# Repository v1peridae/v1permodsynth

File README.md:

# This is the v1permodsyth

- A modular sythesiser is an electronic music instrument made of different sythesiser modules! (who wouldve guessed)
- They look something like this:

<p align="center">
  <br>
  <sub>(mine doesn't look as fancy but we're getting somewhere lol)</sub>
</p>

### it currently has:
- square vco

- vca

- guitar input

-ar

-4lfo

-fm drums

## more on the process
i've never really made anything this complex so i totally understand if it might not work on the first go but i'm really happy with how far i've gotten with this. if you'd like to learn more about the making process check out my JOURNAL.md 

credits to https://www.bartonmusicalcircuits.com/ which is where i learnt how to do all of this :)

casing - it currently doesnt have a case but i have all the measurements and hope to build a wooden or hard cardboard case

note on commits:
guh it totally skipped my mind to make frequent commits of this so i accept my fate if it means my hours get reduced since this is one is on me.

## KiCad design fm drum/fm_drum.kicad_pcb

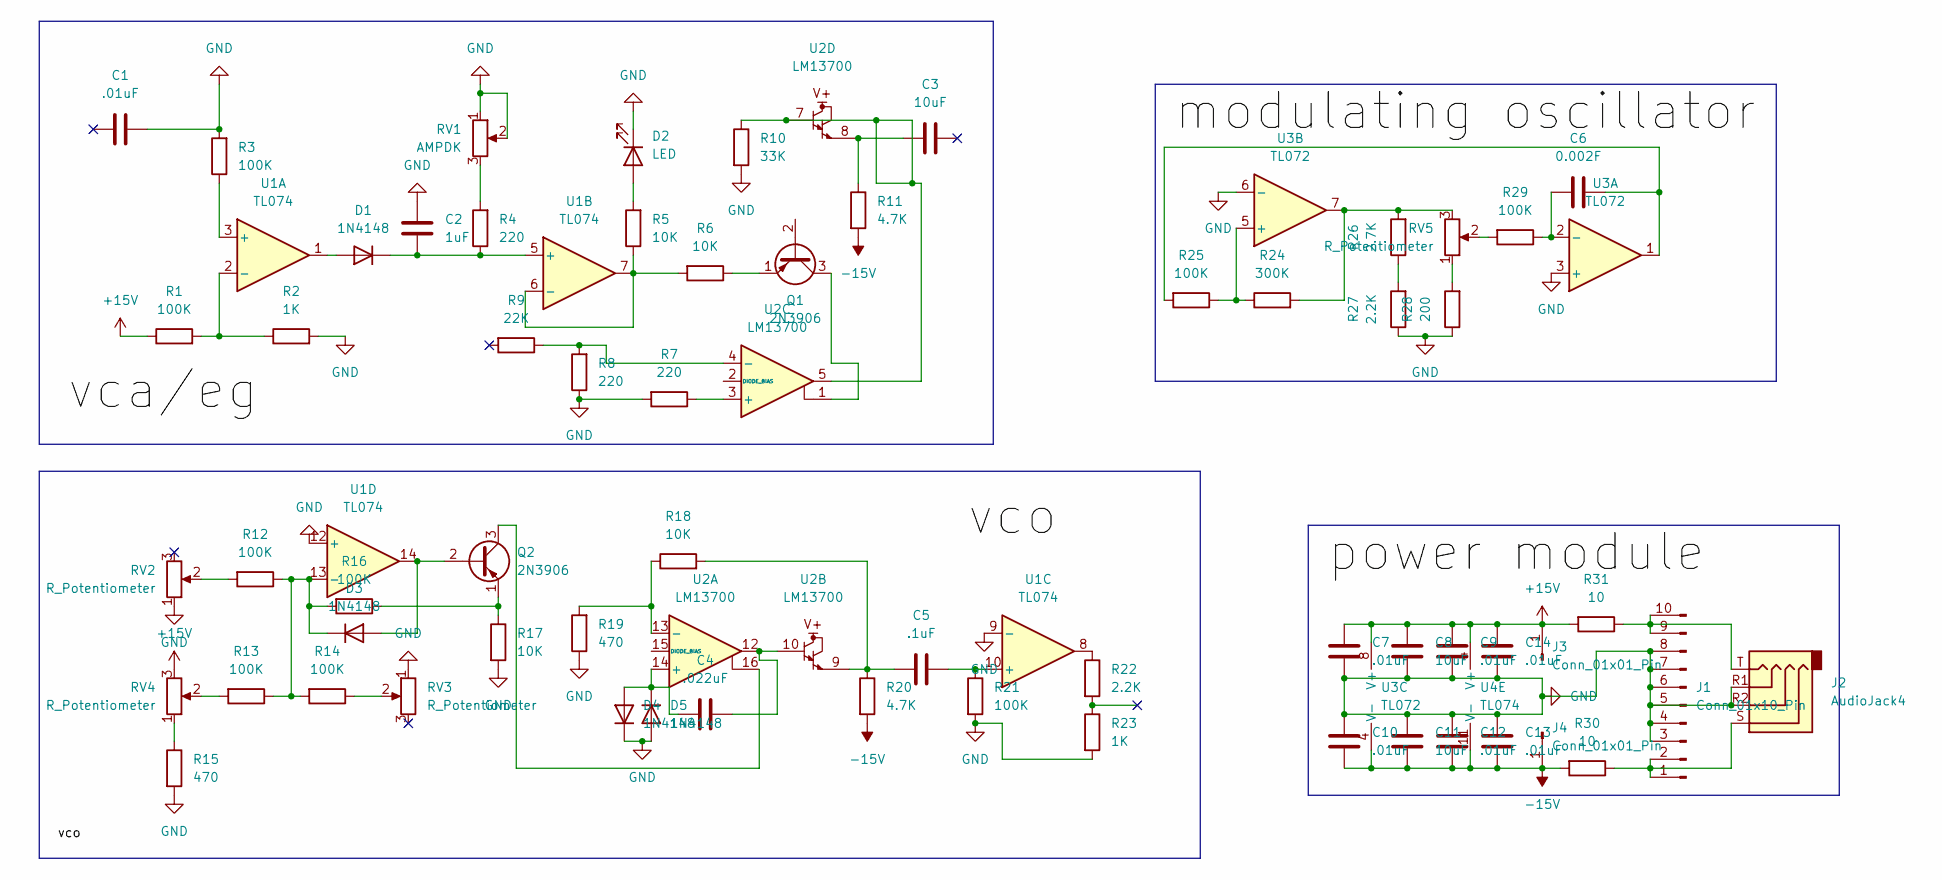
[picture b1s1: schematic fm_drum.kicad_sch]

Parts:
C1, C7, C9, C10, C12, C13, C14: .01uF; C_Disc_D3.8mm_W2.6mm_P2.50mm
C2: 1uF; CP_Radial_D5.0mm_P2.00mm
C3, C8, C11: 10uF; CP_Radial_D5.0mm_P2.50mm
C4: .022uF; C_Rect_L7.2mm_W2.5mm_P5.00mm_FKS2_FKP2_MKS2_MKP2
C5: .1uF; C_Rect_L7.2mm_W2.5mm_P5.00mm_FKS2_FKP2_MKS2_MKP2
C6: 0.002F; C_Rect_L7.2mm_W2.5mm_P5.00mm_FKS2_FKP2_MKS2_MKP2
D1, D3, D4, D5: 1N4148; D_DO-35_SOD27_P7.62mm_Horizontal
D2: LED; LED_D3.0mm
J1: Conn_01x10_Pin; IDC-Header_2x05_P2.54mm_Vertical
J2: AudioJack4; Jack_3.5mm_QingPu_WQP-PJ398SM_Vertical_CircularHoles
J3, J4: Conn_01x01_Pin; PinHeader_1x01_P2.54mm_Horizontal
Q1, Q2: 2N3906; TO-92_Inline
R1, R3, R12, R13, R14, R16, R21, R25, R29: 100K; R_Axial_DIN0207_L6.3mm_D2.5mm_P7.62mm_Horizontal
R2, R23: 1K; R_Axial_DIN0207_L6.3mm_D2.5mm_P7.62mm_Horizontal
R4, R7, R8: 220; R_Axial_DIN0207_L6.3mm_D2.5mm_P7.62mm_Horizontal
R5, R6, R17, R18: 10K; R_Axial_DIN0207_L6.3mm_D2.5mm_P7.62mm_Horizontal
R9: 22K; R_Axial_DIN0207_L6.3mm_D2.5mm_P7.62mm_Horizontal
R10: 33K; R_Axial_DIN0207_L6.3mm_D2.5mm_P7.62mm_Horizontal
R11, R20: 4.7K; R_Axial_DIN0207_L6.3mm_D2.5mm_P7.62mm_Horizontal
R15, R19: 470; R_Axial_DIN0207_L6.3mm_D2.5mm_P7.62mm_Horizontal
R22, R27: 2.2K; R_Axial_DIN0207_L6.3mm_D2.5mm_P7.62mm_Horizontal
R24: 300K; R_Axial_DIN0207_L6.3mm_D2.5mm_P7.62mm_Horizontal
R26: 2.7K; R_Axial_DIN0207_L6.3mm_D2.5mm_P7.62mm_Horizontal
R28: 200; R_Axial_DIN0207_L6.3mm_D2.5mm_P7.62mm_Horizontal
R30, R31: 10; R_Axial_DIN0207_L6.3mm_D2.5mm_P7.62mm_Horizontal
RV1: AMPDK; Potentiometer_Alps_RK163_Single_Horizontal
RV2, RV3, RV4, RV5: R_Potentiometer; Potentiometer_Alps_RK163_Single_Horizontal
U1, U4: TL074; DIP-14_W7.62mm
U2: LM13700; SOIC-16_3.9x9.9mm_P1.27mm
U3: TL072; DIP-8-16_W7.62mm

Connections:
+15V: C7.2, C8.2, C9.2, C14.2, J3.1, R1.1, R31.2, RV4.3, U3.8 (V+), U4.4 (V+)
-15V: C10.1, C11.1, C12.1, C13.1, J4.1, R11.2, R20.2, R30.2, U3.4 (V-), U4.11 (V-)
GND: C1.2, C2.2, C7.1, C8.1, C9.1, C10.2, C11.2, C12.2, C13.2, C14.1, D2.1 (K), D4.1 (K), D5.2 (A), J1.3, J1.4, J1.5, J1.6, J1.7, J1.8, J2.R1, J2.R2, R2.2, R3.2, R7.2, R8.1, R10.2, R15.2, R17.2, R19.1, R21.2, R23.2, R27.1, R28.1, RV1.1, RV1.2, RV2.1, RV3.1, U1.9 (-), U1.12 (+), U3.3 (+), U3.6 (-)
unnamed: C3.2, R11.1, U2.8
unnamed: C4.2, U2.10, U2.12
unnamed: C5.1, R18.2, R20.1, U2.9
unnamed: C6.2, R25.2, U3.1
unnamed: D1.2 (A), U1.1
unnamed: C2.1, D1.1 (K), R4.1, U1.5 (+)
unnamed: D2.2 (A), R5.2
unnamed: D3.2 (A), Q2.2 (B), U1.14
unnamed: D3.1 (K), R12.1, R13.1, R14.2, R16.2, U1.13 (-)
unnamed: C4.1, D4.2 (A), D5.1 (K), U2.14 (+)
unnamed: J1.1, J1.2, J2.S, R30.1
unnamed: J1.9, J1.10, J2.T, R31.1
unnamed: Q1.3 (C), U2.1
unnamed: Q1.1 (E), R6.1
unnamed: Q2.3 (C), U2.16
unnamed: Q2.1 (E), R16.1, R17.1
unnamed: R4.2, RV1.3
unnamed: R10.1, U2.5, U2.7
unnamed: R12.2, RV2.2
unnamed: R13.2, RV4.2
unnamed: R14.1, RV3.2
unnamed: R15.1, RV4.1
unnamed: R22.1, U1.8
unnamed: R24.2, R26.2, RV5.3, U3.7
unnamed: R26.1, R27.2
unnamed: R28.2, RV5.1
unnamed: R29.2, RV5.2
unnamed: R3.1, U1.3 (+)
unnamed: R1.2, R2.1, U1.2 (-)
unnamed: R5.1, R6.2, U1.6 (-), U1.7
unnamed: C5.2, R21.1, U1.10 (+)
unnamed: R18.1, R19.2, U2.13 (-)
unnamed: R7.1, U2.3 (+)
unnamed: R8.2, R9.1, U2.4 (-)
unnamed: C6.1, R29.1, U3.2 (-)
unnamed: R24.1, R25.1, U3.5 (+)

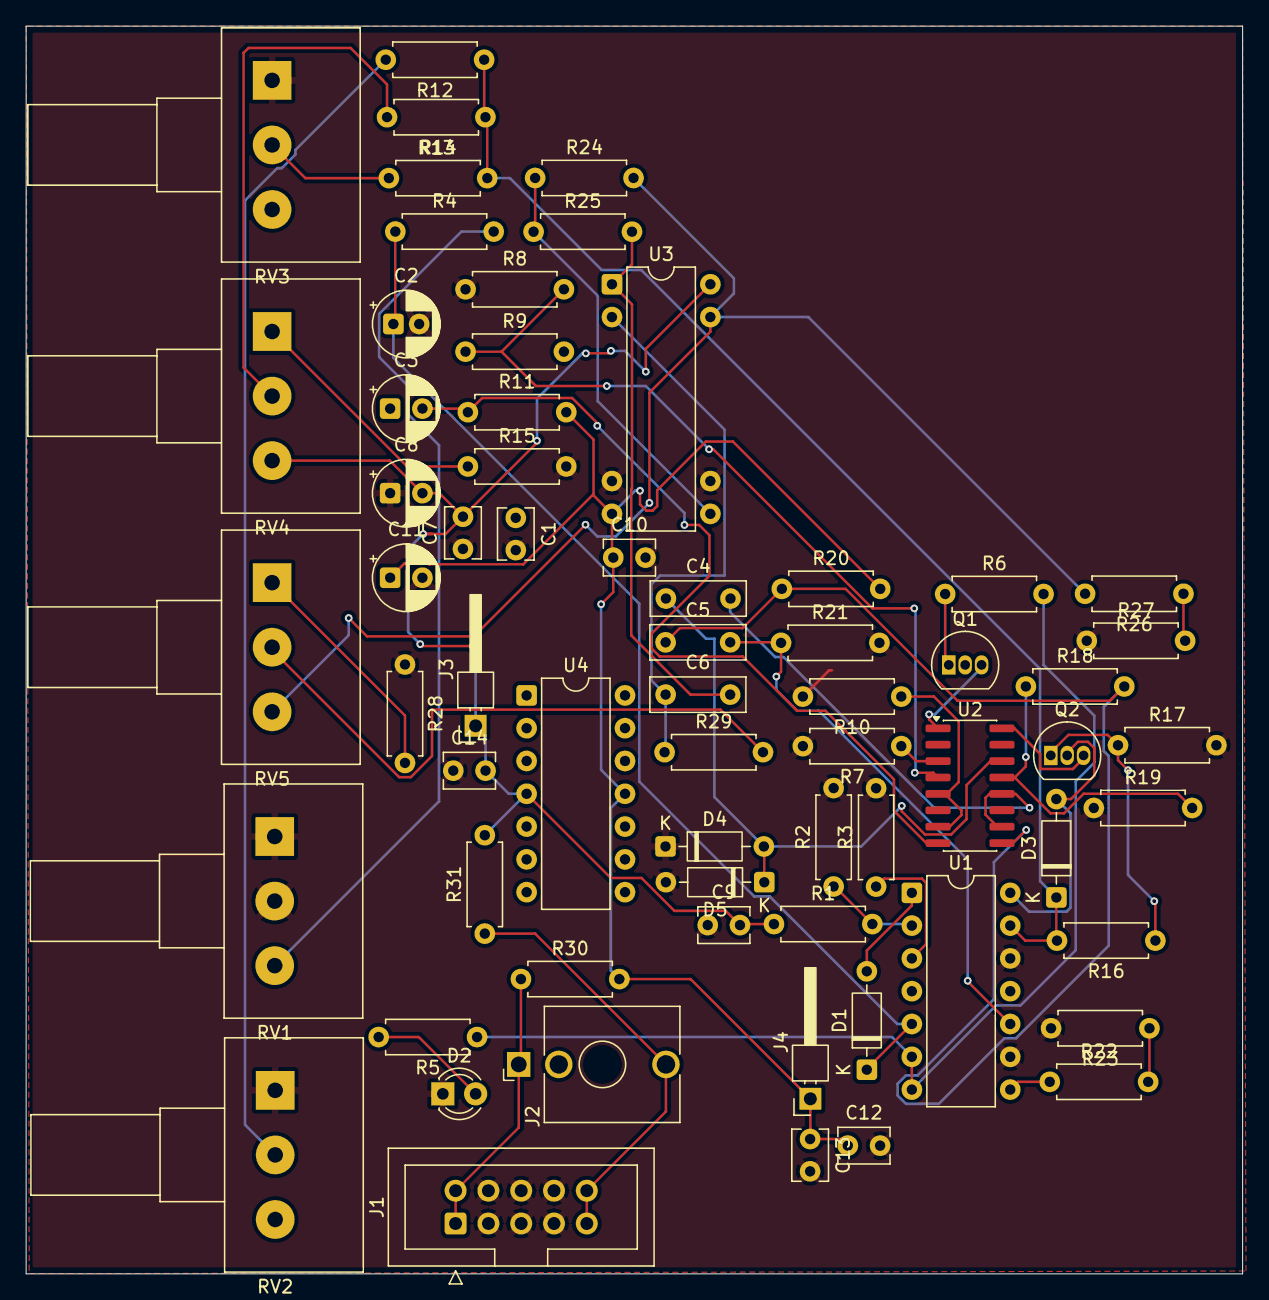
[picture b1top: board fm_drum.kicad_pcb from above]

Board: 2 copper layers, 94.2 x 96.6 mm, 65 parts (0 on the bottom side), 39 nets.

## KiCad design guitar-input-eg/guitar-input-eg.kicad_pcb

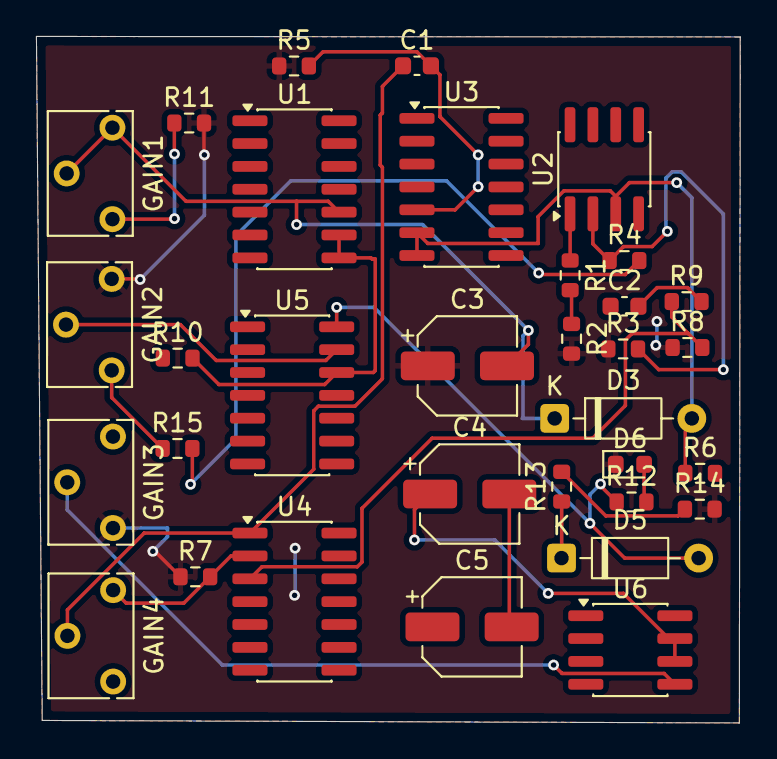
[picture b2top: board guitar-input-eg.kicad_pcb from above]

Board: 2 copper layers, 39.1 x 38.1 mm, 34 parts (1 on the bottom side), 21 nets.

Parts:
.: LOGO
C1, C2: 1uF; C_0603_1608Metric
C3, C4, C5: 10uF; CP_Elec_5x5.4
D3, D5: 1N4148; D_DO-35_SOD27_P7.62mm_Horizontal
D6: LED; LED_0603_1608Metric
GAIN1, GAIN2, GAIN3, GAIN4: A1M; Potentiometer_Bourns_3266W_Vertical
R1, R13: 1.5K; R_0603_1608Metric
R2, R3, R6, R7, R10, R12, R14: 1K; R_0603_1608Metric
R4, R5, R8, R11, R15: 100K; R_0603_1608Metric
R9: 470K; R_0603_1608Metric
U1, U3, U4, U5: TL074; SOIC-14_3.9x8.7mm_P1.27mm
U2, U6: TL072; SOIC-8_3.9x4.9mm_P1.27mm

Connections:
+15V: R4.2, R15.2
GND: C3.1, D6.1 (K), GAIN2.3, GAIN3.1, R2.2, R3.1, R5.1, R7.1, R8.1, R11.2, R14.2
unnamed: C1.1, GAIN4.2, U4.1
unnamed: C2.2, R9.2
unnamed: C4.2, C5.2
unnamed: D3.2 (A), R6.1, U2.3 (+), U3.6 (-), U3.7
unnamed: C3.2, D3.1 (K), GAIN1.2, GAIN1.3, U1.10 (+)
unnamed: D5.2 (A), R12.1, U5.14
unnamed: D5.1 (K), R13.1
unnamed: D6.2 (A), R12.2
unnamed: GAIN1.1, R11.1
unnamed: GAIN2.1, R15.1
unnamed: R1.1, U2.1
unnamed: R10.2, U1.8, U1.9 (-), U5.12 (+)
unnamed: R3.2, R4.1, U2.2 (-)
unnamed: C1.2, R5.2, U3.5 (+)
unnamed: R8.2, R9.1, U4.3 (+)
unnamed: GAIN4.3, R7.2, U4.2 (-)
unnamed: GAIN2.2, U5.13 (-)
unnamed: GAIN3.2, U6.5 (+)
unnamed: C4.1, U6.6 (-), U6.7

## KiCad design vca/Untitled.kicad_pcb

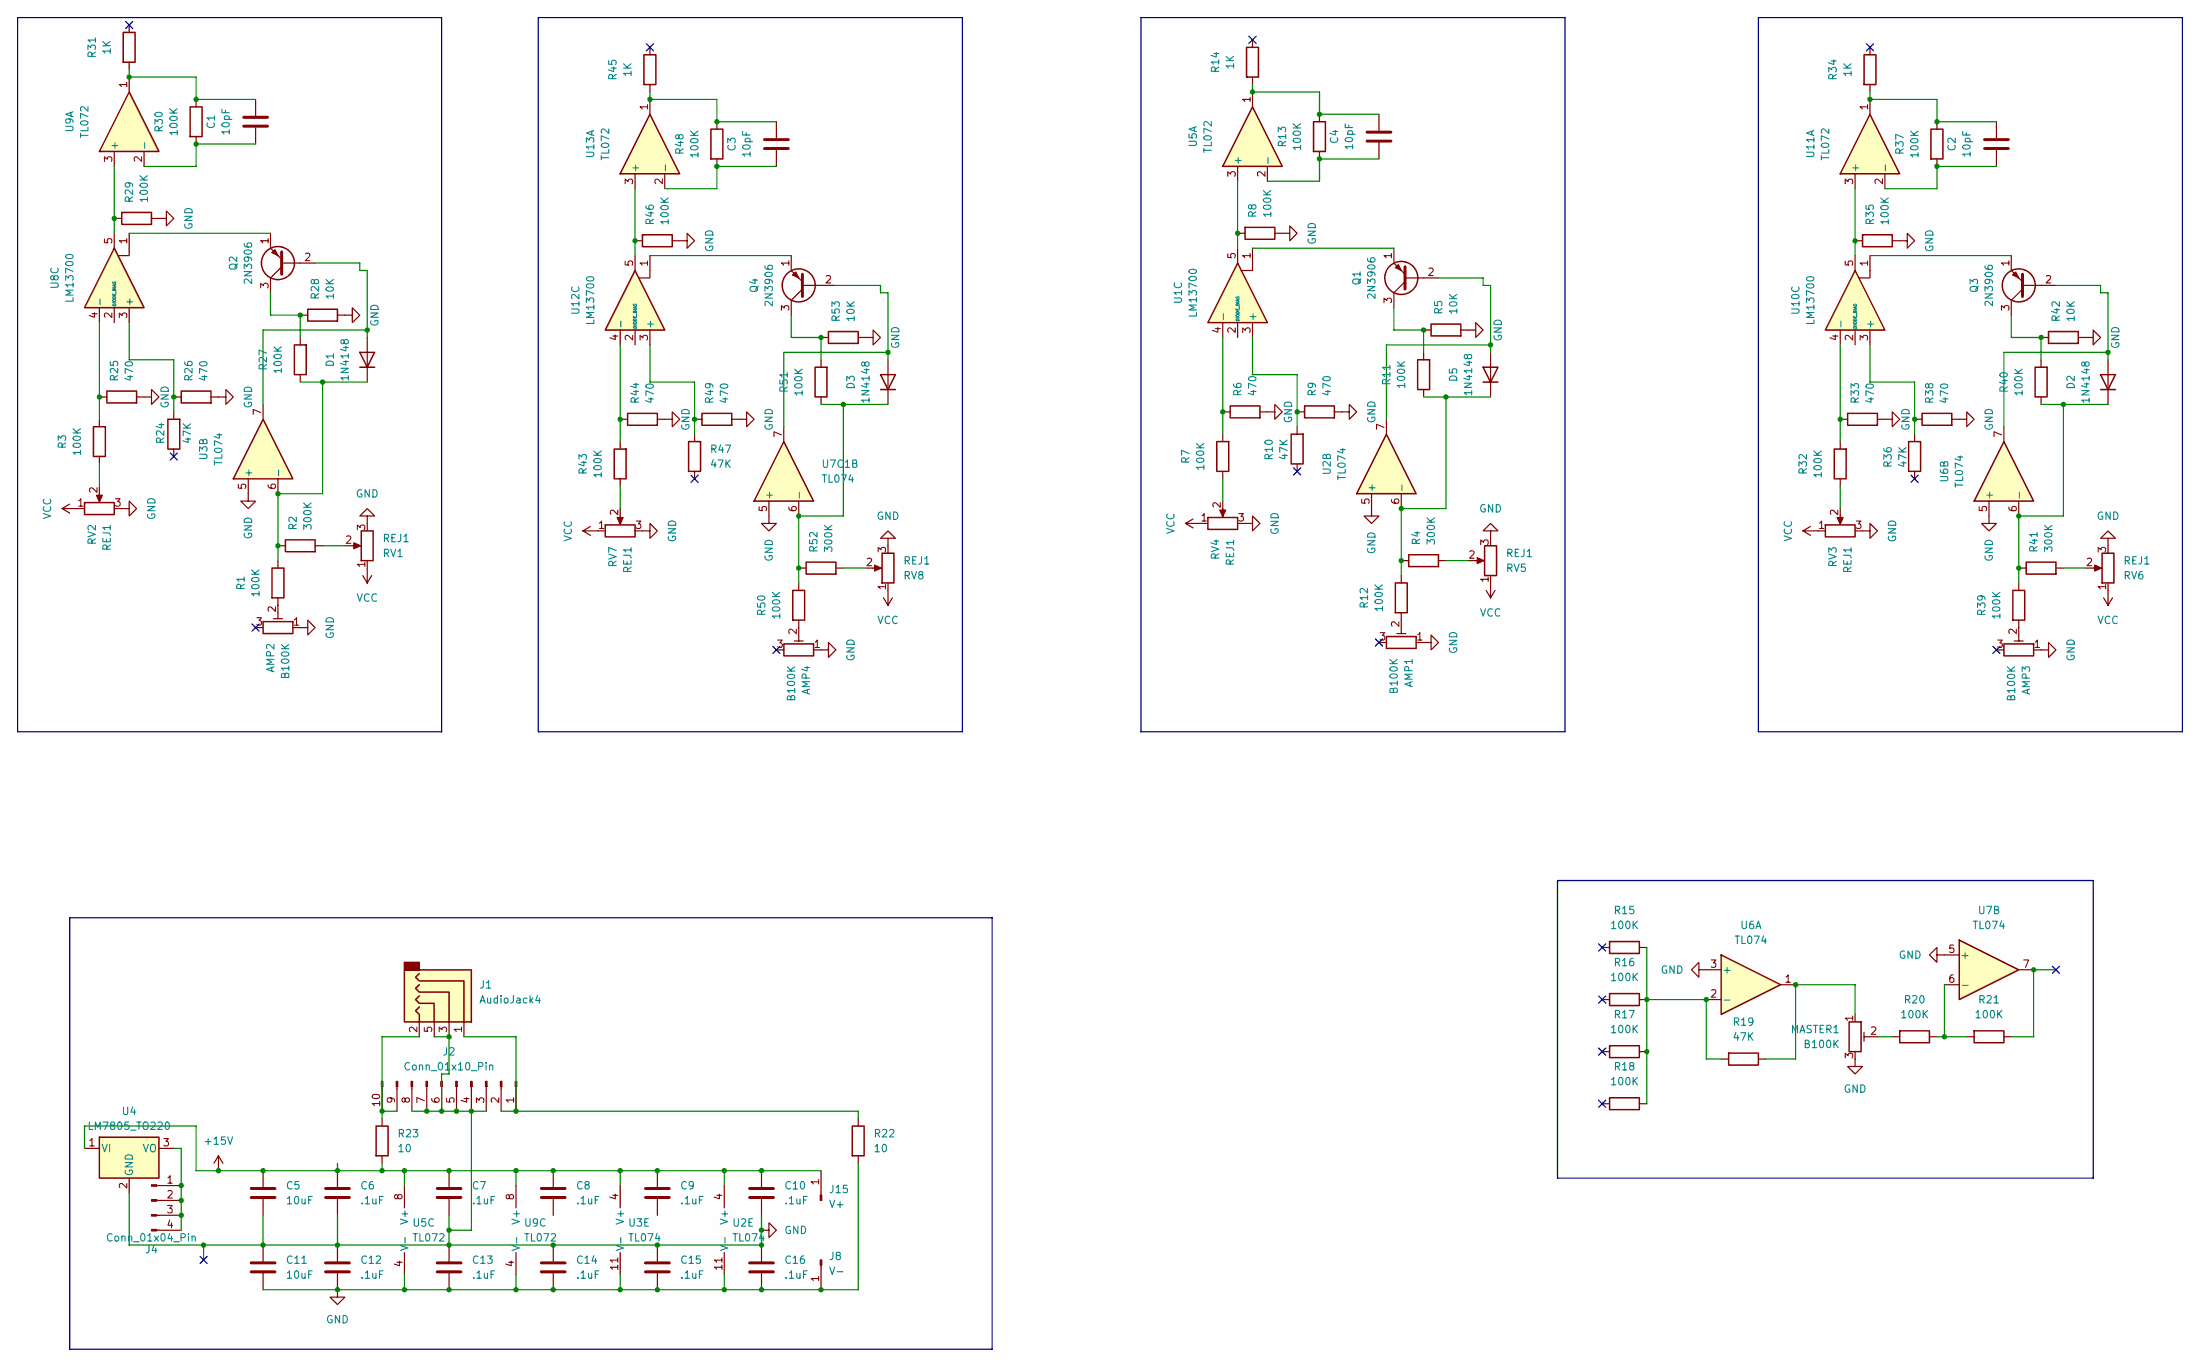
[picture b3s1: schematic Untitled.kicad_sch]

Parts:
AMP1, AMP2, AMP3, AMP4: B100K; Potentiometer_Bourns_3296W_Vertical
C1, C2, C3, C4: 10pF; CP_Elec_5x5.8
C5, C11: 10uF; CP_Elec_5x5.8
C6, C7, C8, C9, C10, C12, C13, C14, C15, C16: .1uF; C_0603_1608Metric
D1, D2, D3, D5: 1N4148; D_DO-35_SOD27_P7.62mm_Horizontal
J1: AudioJack4; Jack_3.5mm_PJ311_Horizontal
J2: Conn_01x10_Pin; IDC-Header_2x05_P2.54mm_Vertical_SMD
J4: Conn_01x04_Pin; PinHeader_1x04_P2.54mm_Vertical
J8: V-; PinHeader_1x01_P2.54mm_Vertical
J15: V+; PinHeader_1x01_P2.54mm_Vertical
MASTER1: B100K; Potentiometer_Bourns_3296W_Vertical
Q1, Q2, Q3, Q4: 2N3906; TO-92_Inline
R1, R3, R7, R8, R11, R12, R13, R15, R16, R17, R18, R20, R21, R27, R29, R30, R32, R35, R37, R39, R40, R43, R46, R48, R50, R51: 100K; R_0603_1608Metric
R2, R4, R41, R52: 300K; R_0603_1608Metric
R5, R28, R42, R53: 10K; R_0603_1608Metric
R6, R9, R25, R26, R33, R38, R44, R49: 470; R_0603_1608Metric
R10, R19, R24, R36, R47: 47K; R_0603_1608Metric
R14, R31, R34, R45: 1K; R_0603_1608Metric
R22, R23: 10; R_0603_1608Metric
RV1, RV2, RV3, RV4, RV5, RV6, RV7, RV8: REJ1; Potentiometer_Bourns_3269P_Horizontal
U1, U8, U10, U12: LM13700; SOIC-16_3.9x9.9mm_P1.27mm
U2, U3, U6, U7, U7C1: TL074; SOIC-14_3.9x8.7mm_P1.27mm
U4: LM7805_TO220; TO-220-3_Vertical
U5, U9, U11, U13: TL072; SOIC-8_3.9x4.9mm_P1.27mm

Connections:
+15V: C5.1, C6.1, C7.1, C8.1, C9.1, C10.1, J15.1, R23.2, U2.4 (V+), U3.4 (V+), U4.1 (VI), U5.8 (V+), U9.8 (V+); also elsewhere on the board
GND: AMP1.1, AMP2.1, AMP3.1, AMP4.1, C5.2, C6.2, C7.2, C10.2, C11.1, C11.2, C12.1, C12.2, C13.1, C13.2, C14.1, C14.2, C15.1, C15.2, C16.1, C16.2, J1.3, J1.5, J2.3, J2.4, J2.5, J2.6, J2.7, J2.8, J8.1, MASTER1.3, R5.2, R6.2, R8.1, R9.2, R22.2, R25.2, R26.2, R28.2, R29.1, R33.2, R35.1, R38.2, R42.2, R44.2, R46.1, R49.2, R53.2, RV1.3, RV2.3, RV3.3, RV4.3, RV5.3, RV6.3, RV7.3, RV8.3, U2.5 (+), U2.11 (V-), U3.5 (+), U3.11 (V-), U4.2 (GND), U5.4 (V-), U6.3 (+), U6.5 (+), U7.5 (+), U7C1.5 (+), U9.4 (V-); also elsewhere on the board
unnamed: AMP1.2, R12.2
unnamed: AMP2.2, R1.2
unnamed: AMP3.2, R39.2
unnamed: AMP4.2, R50.2
unnamed: C1.2, R30.1, R31.2, U9.1
unnamed: C2.2, R34.2, R37.1, U11.1
unnamed: C3.2, R45.2, R48.1, U13.1
unnamed: C4.2, R13.1, R14.2, U5.1
unnamed: D1.2 (A), Q2.2 (B), U3.7
unnamed: D1.1 (K), R1.1, R2.1, R27.1, U3.6 (-)
unnamed: D2.2 (A), Q3.2 (B), U6.7
unnamed: D2.1 (K), R39.1, R40.1, R41.1, U6.6 (-)
unnamed: D3.2 (A), Q4.2 (B), U7C1.7
unnamed: D3.1 (K), R50.1, R51.1, R52.1, U7C1.6 (-)
unnamed: D5.2 (A), Q1.2 (B), U2.7
unnamed: D5.1 (K), R4.1, R11.1, R12.1, U2.6 (-)
unnamed: J1.1, J2.1, J2.2, R22.1
unnamed: J1.2, J2.9, J2.10, R23.1
unnamed: J4.1, J4.2, J4.3, J4.4, U4.3 (VO)
unnamed: MASTER1.1, R19.1, U6.1
unnamed: MASTER1.2, R20.2
unnamed: Q1.3 (C), R5.1, R11.2
unnamed: Q1.1 (E), U1.1
unnamed: Q2.3 (C), R27.2, R28.1
unnamed: Q2.1 (E), U8.1
unnamed: Q3.3 (C), R40.2, R42.1
unnamed: Q3.1 (E), U10.1
unnamed: Q4.3 (C), R51.2, R53.1
unnamed: Q4.1 (E), U12.1
unnamed: R2.2, RV1.2
unnamed: R3.1, RV2.2
unnamed: R4.2, RV5.2
unnamed: R7.1, RV4.2
unnamed: R32.1, RV3.2
unnamed: R41.2, RV6.2
unnamed: R43.1, RV7.2
unnamed: R52.2, RV8.2
unnamed: R9.1, R10.2, U1.3 (+)
unnamed: R6.1, R7.2, U1.4 (-)
unnamed: R8.2, U1.5, U5.3 (+)
unnamed: C4.1, R13.2, U5.2 (-)
unnamed: R15.1, R16.1, R17.1, R18.1, R19.2, U6.2 (-)
unnamed: R20.1, R21.2, U7.6 (-)
unnamed: R24.2, R26.1, U8.3 (+)
unnamed: R3.2, R25.1, U8.4 (-)
unnamed: R29.2, U8.5, U9.3 (+)
unnamed: C1.1, R30.2, U9.2 (-)
unnamed: R36.2, R38.1, U10.3 (+)
unnamed: R32.2, R33.1, U10.4 (-)
unnamed: R35.2, U10.5, U11.3 (+)
unnamed: C2.1, R37.2, U11.2 (-)
unnamed: R47.2, R49.1, U12.3 (+)
unnamed: R43.2, R44.1, U12.4 (-)
unnamed: R46.2, U12.5, U13.3 (+)
unnamed: C3.1, R48.2, U13.2 (-)
VCC: RV1.1, RV2.1, RV3.1, RV4.1, RV5.1, RV6.1, RV7.1, RV8.1

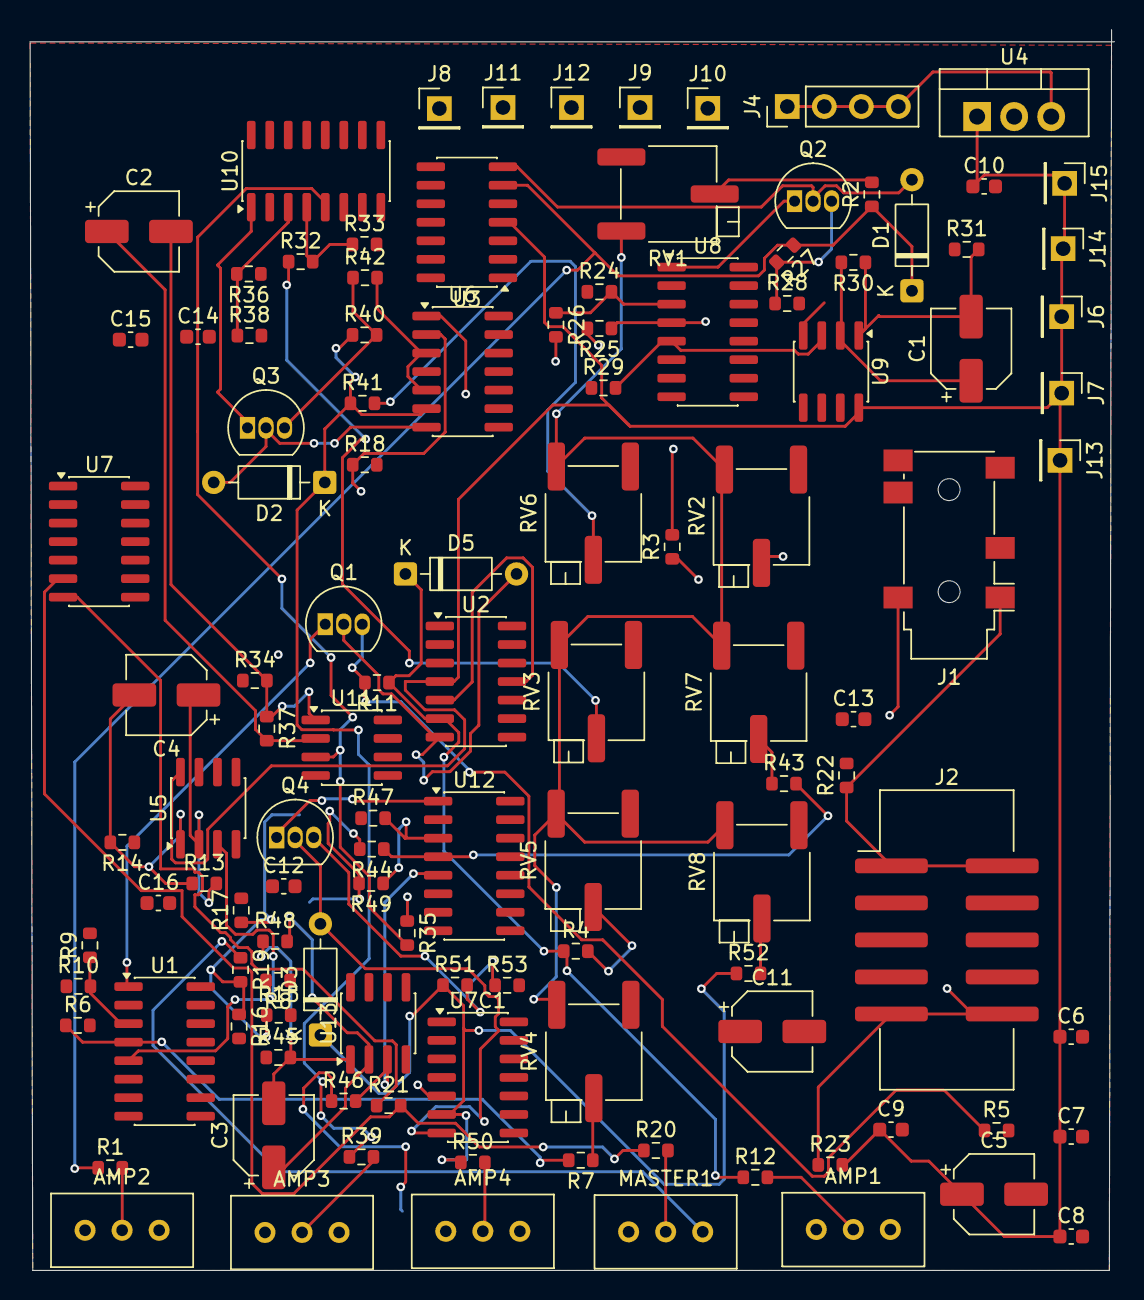
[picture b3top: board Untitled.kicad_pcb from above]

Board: 4 copper layers, 74.4 x 85.1 mm, 117 parts (0 on the bottom side), 58 nets.

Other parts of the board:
J6, J7, J13, J14: V+; PinHeader_1x01_P2.54mm_Vertical
J9, J10, J11, J12: V-; PinHeader_1x01_P2.54mm_Vertical

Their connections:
+15V: J6.1, J7.1, J13.1, J14.1; also elsewhere on the board
GND: J9.1, J10.1, J11.1, J12.1; also elsewhere on the board

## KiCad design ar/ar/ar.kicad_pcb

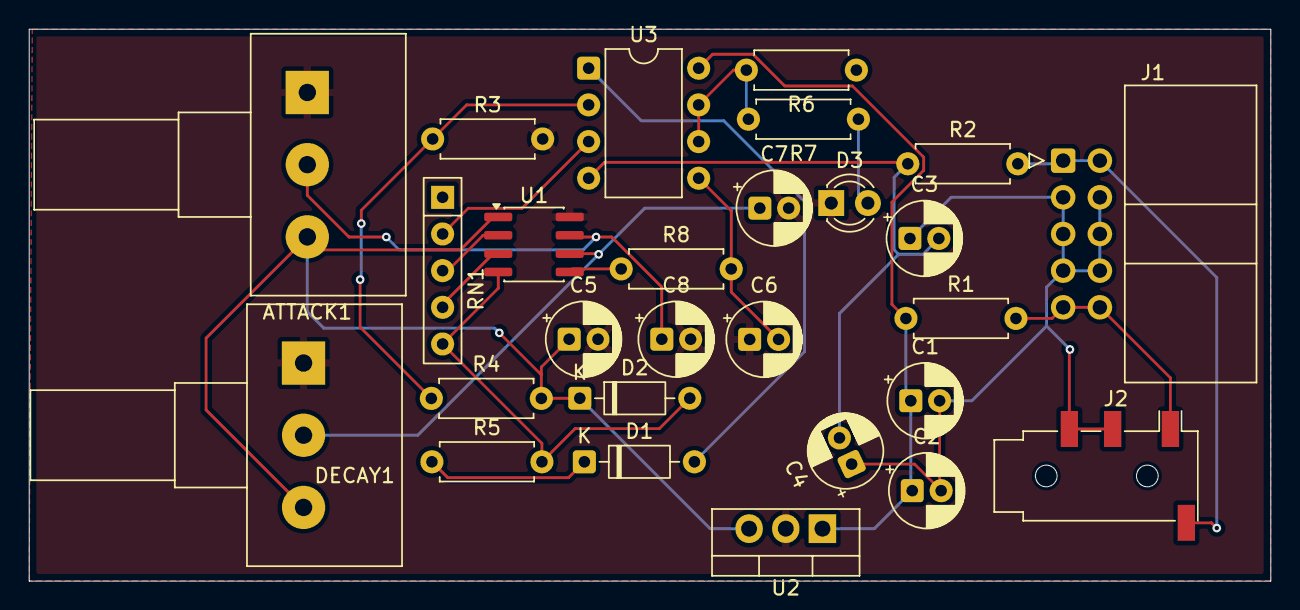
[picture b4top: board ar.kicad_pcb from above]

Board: 2 copper layers, 86.0 x 38.2 mm, 27 parts (0 on the bottom side), 18 nets.

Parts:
ATTACK1: B100K; Potentiometer_Alps_RK163_Single_Horizontal
C1, C3: 10uF; CP_Radial_D5.0mm_P2.00mm
C2, C4, C5, C7, C8: 0.01uF; CP_Radial_D5.0mm_P2.00mm
C6: 0.1uF; CP_Radial_D5.0mm_P2.00mm
D1: 1N4148; D_DO-35_SOD27_P7.62mm_Horizontal
D2: D_Schottky; D_DO-35_SOD27_P7.62mm_Horizontal
D3: LED; LED_D3.0mm
DECAY1: B100K; Potentiometer_Alps_RK163_Single_Horizontal
J1: Conn_01x10_Pin; IDC-Header_2x05_P2.54mm_Horizontal
J2: AudioJack4; Jack_3.5mm_PJ320D_Horizontal
R1, R2: 10; R_Axial_DIN0207_L6.3mm_D2.5mm_P7.62mm_Horizontal
R3, R4, R5: 100K; R_Axial_DIN0207_L6.3mm_D2.5mm_P7.62mm_Horizontal
R6, R7: 1K; R_Axial_DIN0207_L6.3mm_D2.5mm_P7.62mm_Horizontal
R8: 33K; R_Axial_DIN0207_L6.3mm_D2.5mm_P7.62mm_Horizontal
RN1: 100K; R_Array_SIP5
U1: PIC12F683-xSN; SOIC-8_3.9x4.9mm_P1.27mm
U2: L7805; TO-220-3_Vertical
U3: TL072; DIP-8_W7.62mm

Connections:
+5V: ATTACK1.3, C5.1, D2.1 (K), DECAY1.3, R4.2, U1.1 (VDD), U2.3 (OUT)
GND: ATTACK1.1, C5.2, C6.1, C7.2, C8.2, D3.1 (K), DECAY1.1, R3.2, U1.8 (VSS), U2.2 (GND)
unnamed: D1.2 (A), U3.1
unnamed: D1.1 (K), R5.1
unnamed: D2.2 (A), R5.2, RN1.5 (R4), U1.4 (GP3)
unnamed: D3.2 (A), R7.1
unnamed: J1.1, J1.2, J2.S, R2.2
unnamed: C1.2, C2.2, C3.1, C4.1, J1.3, J1.4, J1.5, J1.6, J1.7, J1.8, J2.R1, J2.R2
unnamed: J1.9, J1.10, J2.T, R1.2
unnamed: RN1.2 (R1), U3.3 (+)
unnamed: ATTACK1.2, C8.1, U1.7 (GP0)
unnamed: C7.1, DECAY1.2, U1.6 (GP1)
unnamed: R8.1, U1.5 (GP2)
unnamed: C1.1, C2.1, R1.1, U2.1 (IN), U3.8 (V+)
unnamed: R3.1, R4.1, U3.2 (-)
unnamed: C6.2, R8.2, U3.5 (+)
unnamed: R6.2, R7.2, U3.6 (-), U3.7
unnamed: C3.2, C4.2, R2.1, U3.4 (V-)

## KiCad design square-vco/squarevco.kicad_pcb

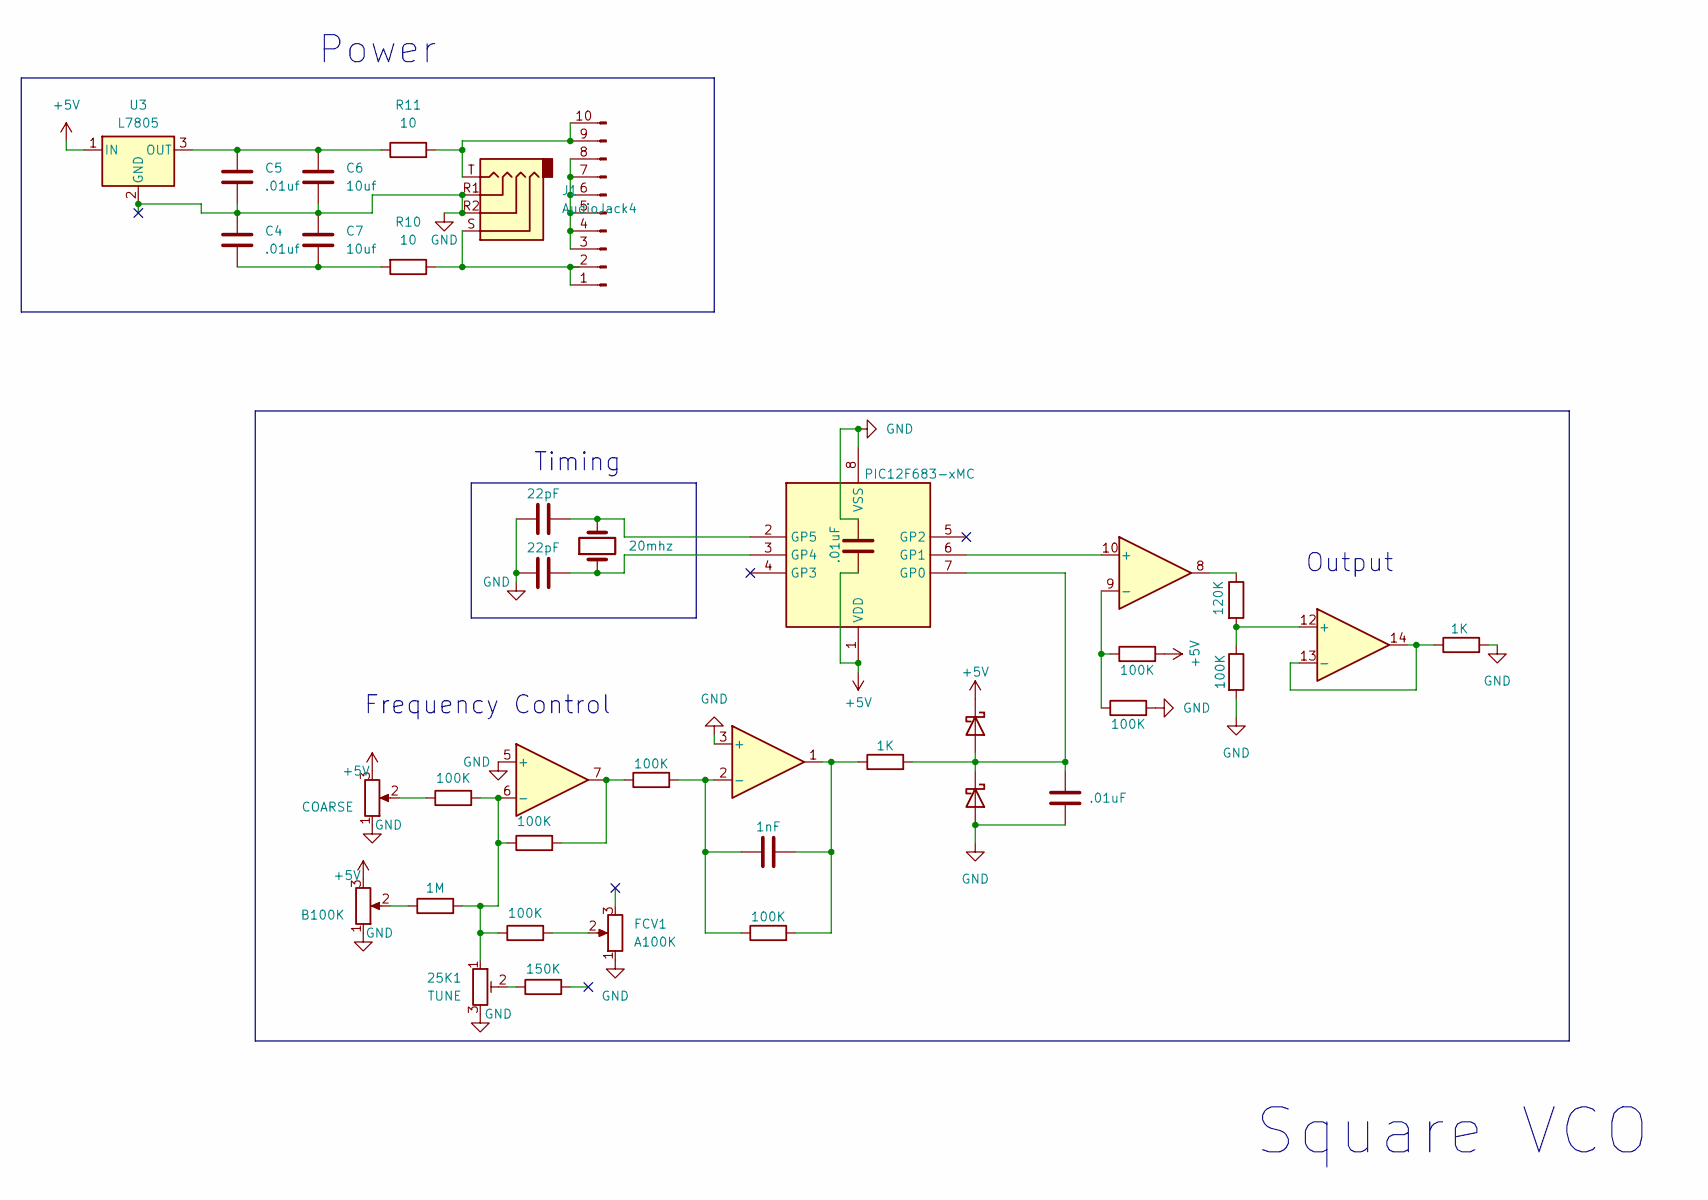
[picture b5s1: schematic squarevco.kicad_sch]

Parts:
25K1: TUNE; Potentiometer_Bourns_3269W_Vertical
B100K1: COARSE; Potentiometer_Alpha_RD901F-40-00D_Single_Vertical
C1, C9: 22pF; C_0805_2012Metric
C2: 1nF; C_0805_2012Metric
C3, C8: .01uF; C_0805_2012Metric
C4, C5: .01uf; C_0805_2012Metric
C6, C7: 10uf; CP_Elec_5x5.4
D1, D2: D_Schottky; D_SOD-123
FCV1: A100K; Potentiometer_Alpha_RD901F-40-00D_Single_Vertical
FINE1: B100K; Potentiometer_Alpha_RD901F-40-00D_Single_Vertical
J1: AudioJack4; Jack_3.5mm_QingPu_WQP-PJ398SM_Vertical_CircularHoles
J4: Conn_01x10_Pin; IDC-Header_2x05_P2.54mm_Horizontal
R1: 120K; R_0805_2012Metric
R2, R5, R7, R8, R14, R16, R17, R18: 100K; R_0805_2012Metric
R3, R4: 1K; R_0805_2012Metric
R6: 1M; R_0805_2012Metric
R10, R11: 10; R_0805_2012Metric
R19: 150K; R_0805_2012Metric
U1: PIC12F683-xMC; SOIC-8_3.9x4.9mm_P1.27mm
U2, U4, U5, U6: TL074; SOIC-14_3.9x8.7mm_P1.27mm
U3: L7805; SOT-223-3_TabPin2
Y1: 20mhz; Crystal_SMD_5032-2Pin_5.0x3.2mm

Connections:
+5V: B100K1.3, C8.2, D1.1 (K), FINE1.3, R7.2, U1.1 (VDD), U3.1 (IN)
GND: 25K1.3, B100K1.1, C1.2, C3.2, C4.1, C5.2, C6.2, C7.1, C8.1, C9.1, D2.2 (A), FCV1.1, FINE1.1, J1.R1, J1.R2, R2.2, R3.2, R8.2, U1.8 (VSS), U3.2 (GND), U5.5 (+), U6.3 (+); also elsewhere on the board
unnamed: 25K1.2, R19.1
unnamed: B100K1.2, R17.1
unnamed: C2.2, R4.1, R5.2, U6.1
unnamed: C4.2, C7.2, R10.2
unnamed: C3.1, D1.2 (A), D2.1 (K), R4.2, U1.7 (GP0)
unnamed: FCV1.2, R18.2
unnamed: FINE1.2, R6.1
unnamed 9: J1.S, J4.1, J4.2, R10.1; also elsewhere on the board
unnamed: J4.3, J4.4, J4.5, J4.6, J4.7, J4.8
unnamed 11: J1.T, J4.9, J4.10, R11.2; also elsewhere on the board
unnamed: R1.1, U2.8
unnamed: R14.1, R16.2, U5.7
unnamed: U1.6 (GP1), U2.10 (+)
unnamed: C1.1, U1.3 (GP4), Y1.1
unnamed: C9.2, U1.2 (GP5), Y1.2
unnamed: R7.1, R8.1, U2.9 (-)
unnamed: C5.1, C6.1, R11.1, U3.3 (OUT)
unnamed: R1.2, R2.1, U4.12 (+)
unnamed: R3.1, U4.13 (-), U4.14
unnamed: 25K1.1, R6.2, R16.1, R17.2, R18.1, U5.6 (-)
unnamed: C2.1, R5.1, R14.2, U6.2 (-)

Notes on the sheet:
Power
Timing
Frequency Control
Square VCO
Output

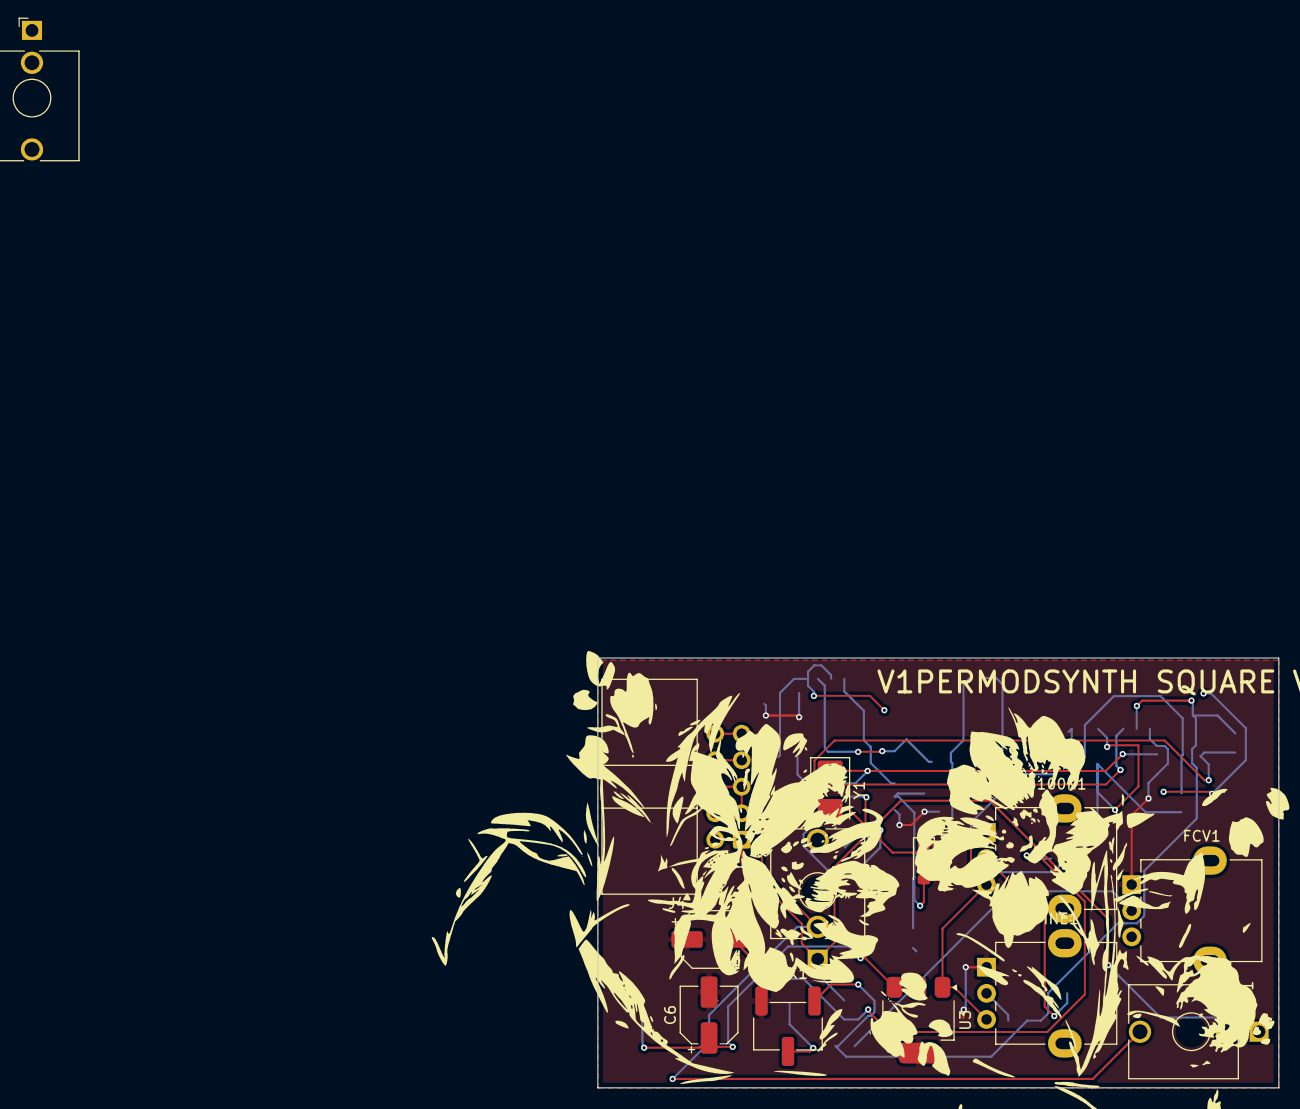
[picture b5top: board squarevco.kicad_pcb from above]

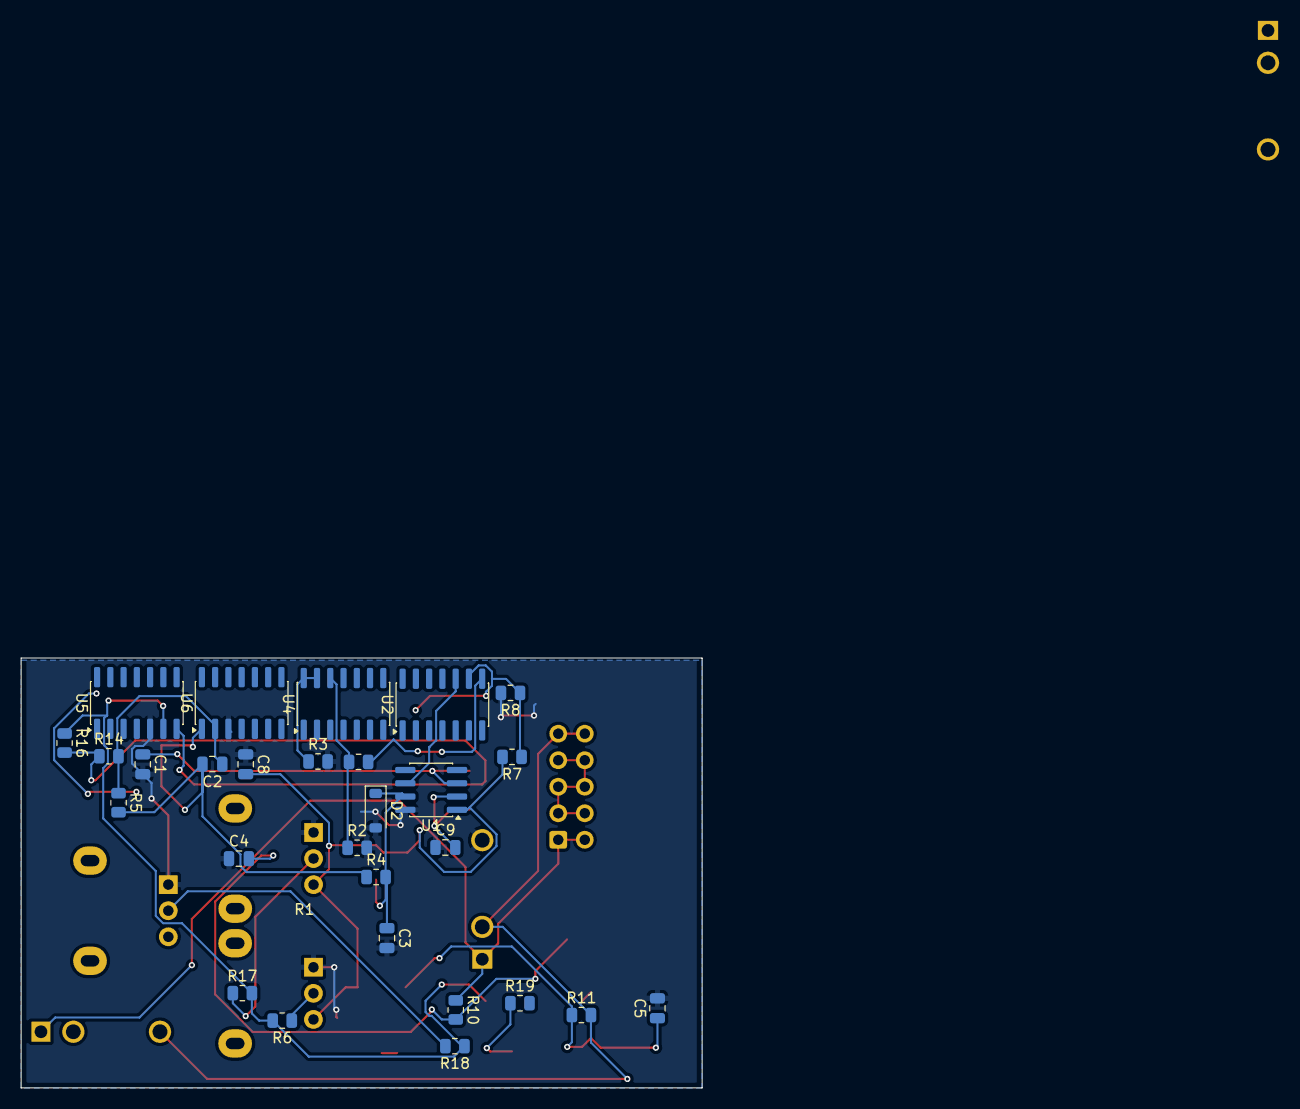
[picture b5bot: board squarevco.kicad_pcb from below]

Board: 2 copper layers, 65.2 x 41.2 mm, 41 parts (28 on the bottom side), 23 nets.

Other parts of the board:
J1#2: AudioJack2_Dual_Switch; Jack_3.5mm_QingPu_WQP-PJ398SM_Vertical_CircularHoles
J5: AudioJack3_SwitchT; Jack_3.5mm_QingPu_WQP-PJ398SM_Vertical_CircularHoles

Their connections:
GND: J5.T; also elsewhere on the board
unnamed 9: J5.S; also elsewhere on the board
unnamed 11: J5.TN; also elsewhere on the board
